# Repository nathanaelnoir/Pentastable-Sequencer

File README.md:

# Pentastable Sequencer 

# Pentastable Sequencer is a 5-step Eurorack sequencer inspired by the Buchla Sound Easel.

## Contents

- Overview
- Features
- Build & assembly notes
- Testing
- License & contributing

## Overview

This repository contains the KiCad 9 design files for Pentastable Sequencer. The module is built around an `Arduino Nano` with a `TL072` handling the analog output stage. Five pots set the sequence voltages, five LEDs show the active step, `TRIG IN` and `RESET IN` let the module sync to the rack, and `CV OUT` plus `TRIG OUT` bring the sequence back out.

The front panel also carries five step toggles, one `TEMPO` pot for the internal clock, one extra pot in the CV output section, and two center-off mode switches wired as `3st / off / 5st` and `FWD / off / RND_TIE`.

Revision in the KiCad title block is `v1.0`, dated `2026-03-13`.

## Features

- 5-step sequencer built around `Arduino Nano v3.x` and `TL072`.
- Five 10 k step pots: `CV1` to `CV5`.
- Five step LEDs for position indication.
- Internal clock with dedicated `TEMPO` control.
- External `TRIG IN` and `RESET IN`.
- Separate `CV OUT` and `TRIG OUT`.
- Five panel toggles tied to the individual stage outputs: `OUT1` to `OUT5`.
- Center-off mode switches for stage count (`3st` / `5st`) and playback behavior (`FWD` / `RND_TIE`).
- Eurorack power sheet using `+12V`, `-12V`, `+5V`, and `GND` on a 16-pin IDC connector.
- Mixed build with SMD passives and ICs plus through-hole panel hardware.

## Build & assembly notes

- Check `A1` orientation and header alignment before soldering the `Arduino Nano`.
- Check `U1` orientation before soldering the `TL072`.
- Double-check the Eurorack power header orientation before first power-up.
- The panel hardware count is not small: four 3.5 mm jacks, seven potentiometers, seven toggle switches, and five LEDs.
- `SW6` and `SW7` are center-off switches. The schematic note calls this out explicitly because the symbol can look misleading if you read it too quickly.
- The output side uses a buffered CV stage around `U1`, `R7`, `R8`, and the extra panel pot. If you change values there, expect the CV output behavior to change with it.

## Testing

1. Program the `Arduino Nano` with the matching firmware before expecting the module to run. This repository does not include that firmware.
2. Power the module from a current-limited Eurorack supply and verify `+12V`, `-12V`, `+5V`, and `GND` first.
3. Turn the internal `TEMPO` control and confirm the step LEDs advance.
4. Feed a pulse into `TRIG IN` and confirm the sequencer advances from the external trigger.
5. Trigger `RESET IN` and confirm the sequence returns to the first stage.
6. Check `CV OUT` and `TRIG OUT` with a scope or a known-good downstream module.

## License & contributing

No `LICENSE` file has been added to this repository yet. Until that changes, assume the design is shared for reference and not under an explicit open-source license.

$$ \huge \prod_{\star}^5 $$

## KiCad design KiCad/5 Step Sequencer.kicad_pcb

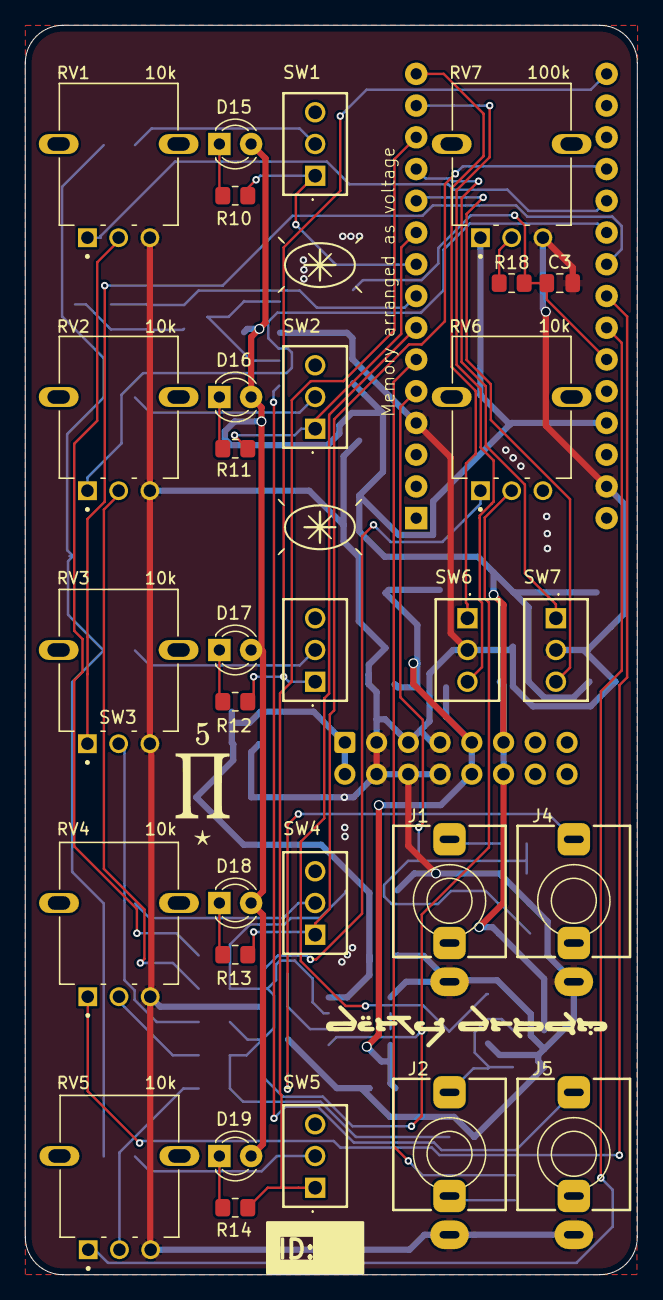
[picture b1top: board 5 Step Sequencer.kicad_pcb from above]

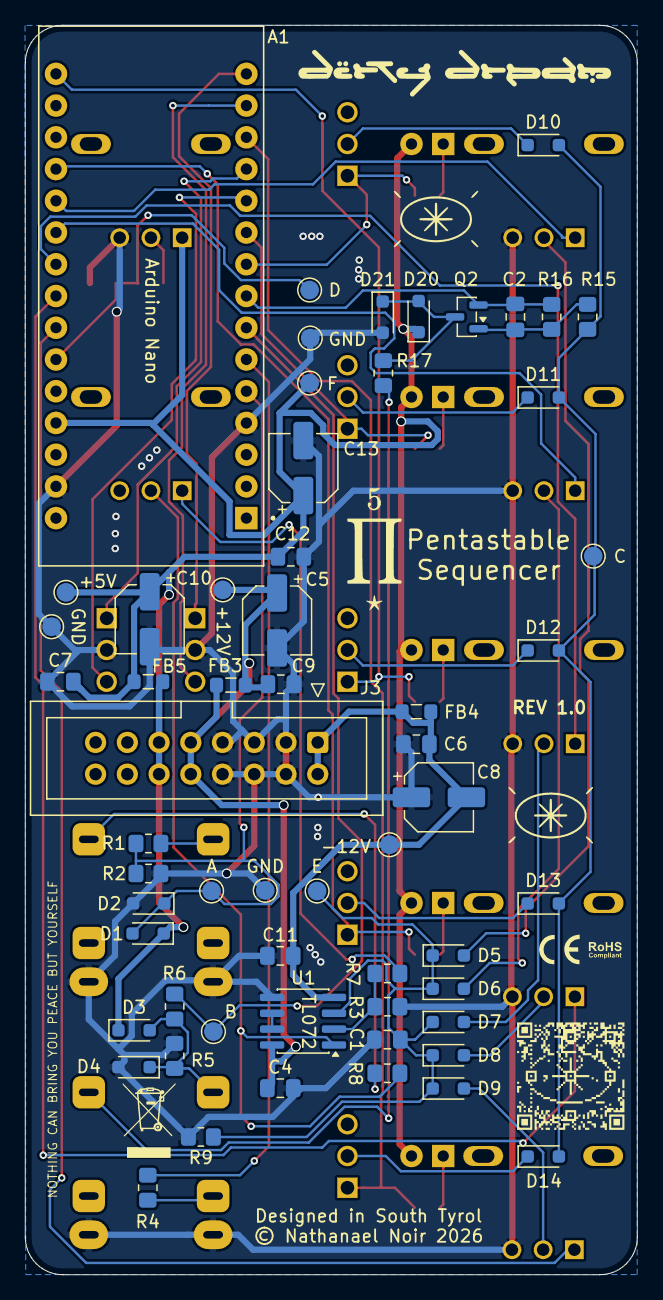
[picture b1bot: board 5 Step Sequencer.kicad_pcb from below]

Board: 2 copper layers, 49.0 x 100.0 mm, 87 parts (57 on the bottom side), 52 nets.

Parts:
 : E; TestPoint_Pad_D1.5mm
 #2: C; TestPoint_Pad_D1.5mm
 #3,  #9,  #10: GND; TestPoint_Pad_D1.5mm
 #4: +5V; TestPoint_Pad_D1.5mm
 #5: D; TestPoint_Pad_D1.5mm
 #6: A; TestPoint_Pad_D1.5mm
 #7: F; TestPoint_Pad_D1.5mm
 #8: +12V; TestPoint_Pad_D1.5mm
A1: Arduino Nano; Arduino_Nano
C1: 10nF; C_0805_2012Metric_Pad1.18x1.45mm_HandSolder
C2: 0.22u; C_0805_2012Metric_Pad1.18x1.45mm_HandSolder
C3: 0.1u; C_0805_2012Metric_Pad1.18x1.45mm_HandSolder
C4, C6, C7, C9, C11, C12: 100nF; C_0805_2012Metric_Pad1.18x1.45mm_HandSolder
C5, C8, C10, C13: 10uF; CP_Elec_5x5.4
D1, D2, D3, D4, D20, D21: BAT43; D_SOD-323_HandSoldering
D5, D6, D7, D8, D9, D10, D11, D12, D13, D14: 1N4148; D_SOD-323_HandSoldering
D15: LED 1; LED_D3.0mm_Clear
D16: LED 2; LED_D3.0mm_Clear
D17: LED 3; LED_D3.0mm_Clear
D18: LED 4; LED_D3.0mm_Clear
D19: LED 5; LED_D3.0mm_Clear
FB3, FB4, FB5: FerriteBead_Small; L_0805_2012Metric_Pad1.05x1.20mm_HandSolder
J1: RESET IN; Jack_3.5mm_QingPu_WQP-PJ398SM_Vertical
J2: TRIG IN; Jack_3.5mm_QingPu_WQP-PJ398SM_Vertical
J3: Connector Header; IDC-Header_2x08_P2.54mm_Vertical
J4: CV OUT; Jack_3.5mm_QingPu_WQP-PJ398SM_Vertical
J5: TRIG OUT; Jack_3.5mm_QingPu_WQP-PJ398SM_Vertical
Q2: BC856; SOT-23
R1, R5, R6, R15, R18: 10k; R_0805_2012Metric_Pad1.20x1.40mm_HandSolder
R2, R9: 100k; R_0805_2012Metric_Pad1.20x1.40mm_HandSolder
R3, R7: 4.7k; R_0805_2012Metric_Pad1.20x1.40mm_HandSolder
R4, R16: 2.2k; R_0805_2012Metric_Pad1.20x1.40mm_HandSolder
R8, R17: 1k; R_0805_2012Metric_Pad1.20x1.40mm_HandSolder
R10, R11, R12, R13, R14: 22k; R_0805_2012Metric_Pad1.20x1.40mm_HandSolder
RV1, RV2, RV3, RV4, RV5, RV6: 10k; Potentiometer_Alpha_RD901F_Vertical_Alt
RV7: 100k; Potentiometer_Alpha_RD901F_Vertical_Alt
SW1, SW2, SW3, SW4, SW5, SW6, SW7: SW_SPDT_321; Switch_Toggle_Dailywell_MS1T1B1M2QES_SPDT
U1: TL072; SOIC-8_3.9x4.9mm_P1.27mm

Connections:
3st: A1.14 (D11), SW6.3 (A)
5st: A1.15 (D12), SW6.1 (C)
+5V: #4.1, #7.1, A1.27 (+5V), C7.1, C10.1, C12.1, C13.1, D1.1 (K), D3.1 (K), D15.2 (A), D16.2 (A), D17.2 (A), D18.2 (A), D19.2 (A), D21.1 (K), FB5.1, FB5.2, J3.11, J3.12, RV7.1
+12V: #8.1, C4.1, C5.1, C9.1, FB3.1, FB3.2, J3.9, J3.10, U1.8 (V+)
-12V: C6.2, C8.2, C11.2, FB4.1, FB4.2, J3.1, J3.2, U1.4 (V-)
/JackReset: J1.T, R1.1
/Trigger_DTCT: J2.TN, R4.1
CV1: A1.20 (A1), RV1.1
CV2: A1.21 (A2), RV2.1
CV3: A1.22 (A3), RV3.1
CV4: A1.23 (A4), RV4.1
CV5: A1.24 (A5), RV5.1
FWD: A1.11 (D8), SW7.3 (A)
GND: #3.1, #9.1, #10.1, A1.4 (GND), A1.29 (GND), C1.2, C3.2, C4.2, C5.2, C6.1, C7.2, C8.1, C9.2, C10.2, C11.1, C12.2, C13.2, D2.2 (A), D4.2 (A), D20.2 (A), J1.S, J2.S, J3.3, J3.4, J3.5, J3.6, J3.7, J3.8, J4.S, J5.S, R2.2, R3.2, R5.1, R9.2, RV1.3, RV2.3, RV3.3, RV4.3, RV5.3, RV7.3, SW6.2 (B), SW7.2 (B), U1.5 (+)
unnamed: D3.2 (A), D4.1 (K), J2.T, R5.2, R6.1
unnamed: D5.2 (A), RV1.2
unnamed: .1, C1.1, D5.1 (K), D6.1 (K), D7.1 (K), D8.1 (K), D9.1 (K), R9.1, U1.3 (+)
unnamed: D6.2 (A), RV2.2
unnamed: D7.2 (A), RV3.2
unnamed: D8.2 (A), RV4.2
unnamed: D9.2 (A), RV5.2
unnamed: #2.1, D10.2 (A), D11.2 (A), D12.2 (A), D13.2 (A), D14.2 (A), R15.1
unnamed: D10.1 (K), SW1.2 (B)
unnamed: D11.1 (K), SW2.2 (B)
unnamed: D12.1 (K), SW3.2 (B)
unnamed: D13.1 (K), SW4.2 (B)
unnamed: D14.1 (K), SW5.2 (B)
unnamed: D15.1 (K), R10.1
unnamed: D16.1 (K), R11.1
unnamed: D17.1 (K), R12.1
unnamed: D18.1 (K), R13.1
unnamed: D19.1 (K), R14.1
unnamed: D20.1 (K), D21.2 (A), Q2.3 (C), R17.1
unnamed: J4.T, R8.2
unnamed: J5.T, R17.2
unnamed: C2.2, Q2.1 (B), R15.2, R16.1
unnamed: R7.2, RV6.1
unnamed: R8.1, RV6.2, U1.1
unnamed: R18.1, RV7.2
unnamed: R3.1, R7.1, U1.2 (-)
unnamed: U1.6 (-), U1.7
OUT1: A1.9 (D6), R10.2, SW1.1 (C)
OUT2: A1.10 (D7), R11.2, SW2.1 (C)
OUT3: A1.16 (D13), R12.2, SW3.1 (C)
OUT4: A1.19 (A0), R13.2, SW4.1 (C)
OUT5: A1.13 (D10), R14.2, SW5.1 (C)
RESET IN: #6.1, A1.5 (D2), D1.2 (A), D2.1 (K), R1.2, R2.1
RND_TIE: A1.12 (D9), SW7.1 (C)
TEMPO: #5.1, A1.25 (A6), C3.1, R18.2
TRIGGER DTCT: A1.6 (D3), R4.2
TRIGGER IN: A1.7 (D4), R6.2
TRIGGER OUT: A1.8 (D5), C2.1, Q2.2 (E), R16.2

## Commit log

2026-03-12 first commit message
2026-03-12 feat: rework sequencer switch routing and power sheet
    - add step/output/CV trigger labels and rewired connections
    - replace mode switch with DP3T where needed
    - add power symbols and decoupling parts on the power sheet
    - fix KiCad project metadata and rename the power sheet
2026-03-13 feat(kicad): add +5V bulk decoupling and tidy schematic layout
    - add C13 as a 10uF polarized capacitor across +5V and GND
    - add project title/revision metadata and clearer section labels
    - rename the power sheet to "EURORACK POWER"
    - clean up power-sheet wiring, grounding, and text placement
2026-03-13 chore(kicad): annotate component values and tidy step-stage wiring
    - replace placeholder resistor, capacitor, and potentiometer values with real part values
    - clean up wire connections around the D10-D14 step-stage diode network
    - adjust symbol and label placement to match the updated routing
2026-03-13 Changing Sheet Names
2026-03-25 adding some missing footprints
2026-03-25 Changing Toggle Switch Foorptint
2026-03-27 adding last missing footprints
2026-03-27 starting pcb layout
2026-03-28 new footprint for tl072
2026-03-29 routing
2026-03-29 finalizing tracks, strating silkscreen layout
2026-03-29 silkscreen adjustments
2026-03-29 finishing silkscreen
2026-03-30 • docs: rewrite README for Pentastable Sequencer with badges and KiCad-based module details
2026-04-02 adding new logo, troubleshooting, gerber
2026-04-02 changing folder name
2026-04-02 changing file names

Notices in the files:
KiCad/5 Step Sequencer.kicad_pcb:
© Nathanael Noir 2026
README.md:
License: TBD
